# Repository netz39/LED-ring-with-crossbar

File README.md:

# LED ring with crossbar

This ring contains 32 addressable LEDs and 10 also addressable LEDs as crossbar.

This is part of [Stepper-Locking-System](https://github.com/netz39/Stepper-Locking-System).

The CAD models are here: [OnShape](https://cad.onshape.com/documents/e2d30949799f050b252632fe/w/72c412dc9c1a5764811a9783/e/a3e88e734353b2ea9fe2e731)
--

Requirements for v1.0
--

* sychronous addressable LEDs (APA102 or SK9822)
* two connectors, one input and one output for cascading
* two mounting holes

Pictures (v1.0)
--

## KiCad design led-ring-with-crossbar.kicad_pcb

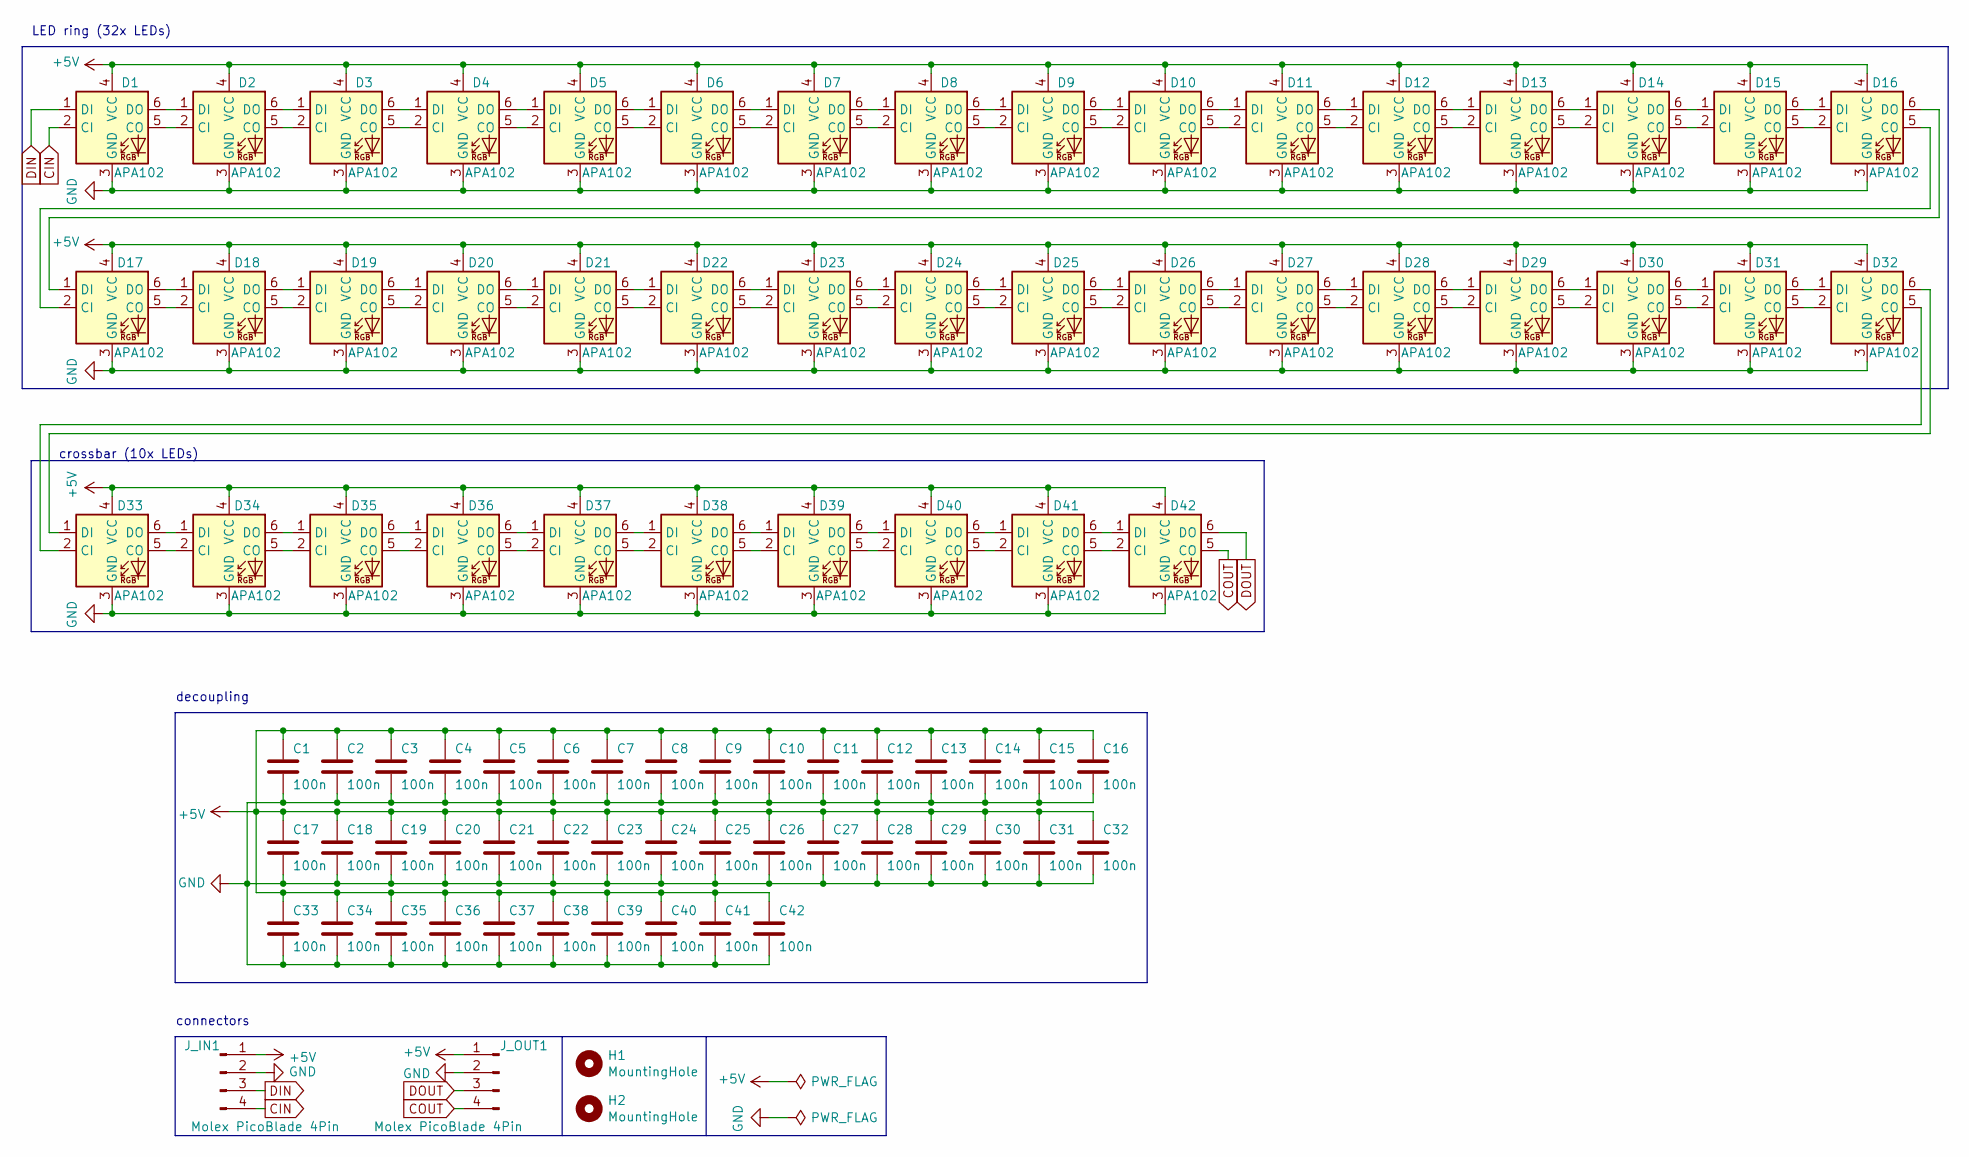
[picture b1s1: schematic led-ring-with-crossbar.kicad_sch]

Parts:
C1, C2, C3, C4, C5, C6, C7, C8, C9, C10, C11, C12, C13, C14, C15, C16, C17, C18, C19, C20, C21, C22, C23, C24, C25, C26, C27, C28, C29, C30, C31, C32, C33, C34, C35, C36, C37, C38, C39, C40, C41, C42: 100n; C_0603_1608Metric
D1, D2, D3, D4, D5, D6, D7, D8, D9, D10, D11, D12, D13, D14, D15, D16, D17, D18, D19, D20, D21, D22, D23, D24, D25, D26, D27, D28, D29, D30, D31, D32, D33, D34, D35, D36, D37, D38, D39, D40, D41, D42: APA102; LED_RGB_5050-6
H1, H2: MountingHole; MountingHole_3.2mm_M3_ISO7380_Keepout
J_IN1: Molex PicoBlade 4Pin; Molex_PicoBlade_53047-0410_1x04_P1.25mm_Vertical
J_OUT1: Molex PicoBlade 4Pin; Molex_PicoBlade_53047-0410_1x04_P1.25mm_Vertical

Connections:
+5V: C1.1, C2.1, C3.1, C4.1, C5.1, C6.1, C7.1, C8.1, C9.1, C10.1, C11.1, C12.1, C13.1, C14.1, C15.1, C16.1, C17.1, C18.1, C19.1, C20.1, C21.1, C22.1, C23.1, C24.1, C25.1, C26.1, C27.1, C28.1, C29.1, C30.1, C31.1, C32.1, C33.1, C34.1, C35.1, C36.1, C37.1, C38.1, C39.1, C40.1, C41.1, C42.1, D1.4 (VCC), D2.4 (VCC), D3.4 (VCC), D4.4 (VCC), D5.4 (VCC), D6.4 (VCC), D7.4 (VCC), D8.4 (VCC), D9.4 (VCC), D10.4 (VCC), D11.4 (VCC), D12.4 (VCC), D13.4 (VCC), D14.4 (VCC), D15.4 (VCC), D16.4 (VCC), D17.4 (VCC), D18.4 (VCC), D19.4 (VCC), D20.4 (VCC), D21.4 (VCC), D22.4 (VCC), D23.4 (VCC), D24.4 (VCC), D25.4 (VCC), D26.4 (VCC), D27.4 (VCC), D28.4 (VCC), D29.4 (VCC), D30.4 (VCC), D31.4 (VCC), D32.4 (VCC), D33.4 (VCC), D34.4 (VCC), D35.4 (VCC), D36.4 (VCC), D37.4 (VCC), D38.4 (VCC), D39.4 (VCC), D40.4 (VCC), D41.4 (VCC), D42.4 (VCC), J_IN1.1, J_OUT1.1
CIN: D1.2 (CI), J_IN1.4
COUT: D42.5 (CO), J_OUT1.4
DIN: D1.1 (DI), J_IN1.3
DOUT: D42.6 (DO), J_OUT1.3
GND: C1.2, C2.2, C3.2, C4.2, C5.2, C6.2, C7.2, C8.2, C9.2, C10.2, C11.2, C12.2, C13.2, C14.2, C15.2, C16.2, C17.2, C18.2, C19.2, C20.2, C21.2, C22.2, C23.2, C24.2, C25.2, C26.2, C27.2, C28.2, C29.2, C30.2, C31.2, C32.2, C33.2, C34.2, C35.2, C36.2, C37.2, C38.2, C39.2, C40.2, C41.2, C42.2, D1.3 (GND), D2.3 (GND), D3.3 (GND), D4.3 (GND), D5.3 (GND), D6.3 (GND), D7.3 (GND), D8.3 (GND), D9.3 (GND), D10.3 (GND), D11.3 (GND), D12.3 (GND), D13.3 (GND), D14.3 (GND), D15.3 (GND), D16.3 (GND), D17.3 (GND), D18.3 (GND), D19.3 (GND), D20.3 (GND), D21.3 (GND), D22.3 (GND), D23.3 (GND), D24.3 (GND), D25.3 (GND), D26.3 (GND), D27.3 (GND), D28.3 (GND), D29.3 (GND), D30.3 (GND), D31.3 (GND), D32.3 (GND), D33.3 (GND), D34.3 (GND), D35.3 (GND), D36.3 (GND), D37.3 (GND), D38.3 (GND), D39.3 (GND), D40.3 (GND), D41.3 (GND), D42.3 (GND), J_IN1.2, J_OUT1.2
unnamed: D1.5 (CO), D2.2 (CI)
unnamed: D1.6 (DO), D2.1 (DI)
unnamed: D2.5 (CO), D3.2 (CI)
unnamed: D2.6 (DO), D3.1 (DI)
unnamed: D3.5 (CO), D4.2 (CI)
unnamed: D3.6 (DO), D4.1 (DI)
unnamed: D4.5 (CO), D5.2 (CI)
unnamed: D4.6 (DO), D5.1 (DI)
unnamed: D5.5 (CO), D6.2 (CI)
unnamed: D5.6 (DO), D6.1 (DI)
unnamed: D6.5 (CO), D7.2 (CI)
unnamed: D6.6 (DO), D7.1 (DI)
unnamed: D7.5 (CO), D8.2 (CI)
unnamed: D7.6 (DO), D8.1 (DI)
unnamed: D8.5 (CO), D9.2 (CI)
unnamed: D8.6 (DO), D9.1 (DI)
unnamed: D9.6 (DO), D10.1 (DI)
unnamed: D9.5 (CO), D10.2 (CI)
unnamed: D10.5 (CO), D11.2 (CI)
unnamed: D10.6 (DO), D11.1 (DI)
unnamed: D11.5 (CO), D12.2 (CI)
unnamed: D11.6 (DO), D12.1 (DI)
unnamed: D12.5 (CO), D13.2 (CI)
unnamed: D12.6 (DO), D13.1 (DI)
unnamed: D13.5 (CO), D14.2 (CI)
unnamed: D13.6 (DO), D14.1 (DI)
unnamed: D14.5 (CO), D15.2 (CI)
unnamed: D14.6 (DO), D15.1 (DI)
unnamed: D15.5 (CO), D16.2 (CI)
unnamed: D15.6 (DO), D16.1 (DI)
unnamed: D16.5 (CO), D17.2 (CI)
unnamed: D16.6 (DO), D17.1 (DI)
unnamed: D17.5 (CO), D18.2 (CI)
unnamed: D17.6 (DO), D18.1 (DI)
unnamed: D18.5 (CO), D19.2 (CI)
unnamed: D18.6 (DO), D19.1 (DI)
unnamed: D19.5 (CO), D20.2 (CI)
unnamed: D19.6 (DO), D20.1 (DI)
unnamed: D20.5 (CO), D21.2 (CI)
unnamed: D20.6 (DO), D21.1 (DI)
unnamed: D21.5 (CO), D22.2 (CI)
unnamed: D21.6 (DO), D22.1 (DI)
unnamed: D22.5 (CO), D23.2 (CI)
unnamed: D22.6 (DO), D23.1 (DI)
unnamed: D23.5 (CO), D24.2 (CI)
unnamed: D23.6 (DO), D24.1 (DI)
unnamed: D24.5 (CO), D25.2 (CI)
unnamed: D24.6 (DO), D25.1 (DI)
unnamed: D25.5 (CO), D26.2 (CI)
unnamed: D25.6 (DO), D26.1 (DI)
unnamed: D26.5 (CO), D27.2 (CI)
unnamed: D26.6 (DO), D27.1 (DI)
unnamed: D27.5 (CO), D28.2 (CI)
unnamed: D27.6 (DO), D28.1 (DI)
unnamed: D28.5 (CO), D29.2 (CI)
unnamed: D28.6 (DO), D29.1 (DI)
unnamed: D29.5 (CO), D30.2 (CI)
unnamed: D29.6 (DO), D30.1 (DI)
unnamed: D30.5 (CO), D31.2 (CI)
unnamed: D30.6 (DO), D31.1 (DI)
unnamed: D31.5 (CO), D32.2 (CI)
unnamed: D31.6 (DO), D32.1 (DI)
unnamed: D32.5 (CO), D33.2 (CI)
unnamed: D32.6 (DO), D33.1 (DI)
unnamed: D33.5 (CO), D34.2 (CI)
unnamed: D33.6 (DO), D34.1 (DI)
unnamed: D34.5 (CO), D35.2 (CI)
unnamed: D34.6 (DO), D35.1 (DI)
unnamed: D35.5 (CO), D36.2 (CI)
unnamed: D35.6 (DO), D36.1 (DI)
unnamed: D36.5 (CO), D37.2 (CI)
unnamed: D36.6 (DO), D37.1 (DI)
unnamed: D37.5 (CO), D38.2 (CI)
unnamed: D37.6 (DO), D38.1 (DI)
unnamed: D38.5 (CO), D39.2 (CI)
unnamed: D38.6 (DO), D39.1 (DI)
unnamed: D39.5 (CO), D40.2 (CI)
unnamed: D39.6 (DO), D40.1 (DI)
unnamed: D40.5 (CO), D41.2 (CI)
unnamed: D40.6 (DO), D41.1 (DI)
unnamed: D41.5 (CO), D42.2 (CI)
unnamed: D41.6 (DO), D42.1 (DI)

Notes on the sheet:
connectors
LED ring (32x LEDs)
crossbar (10x LEDs)
decoupling

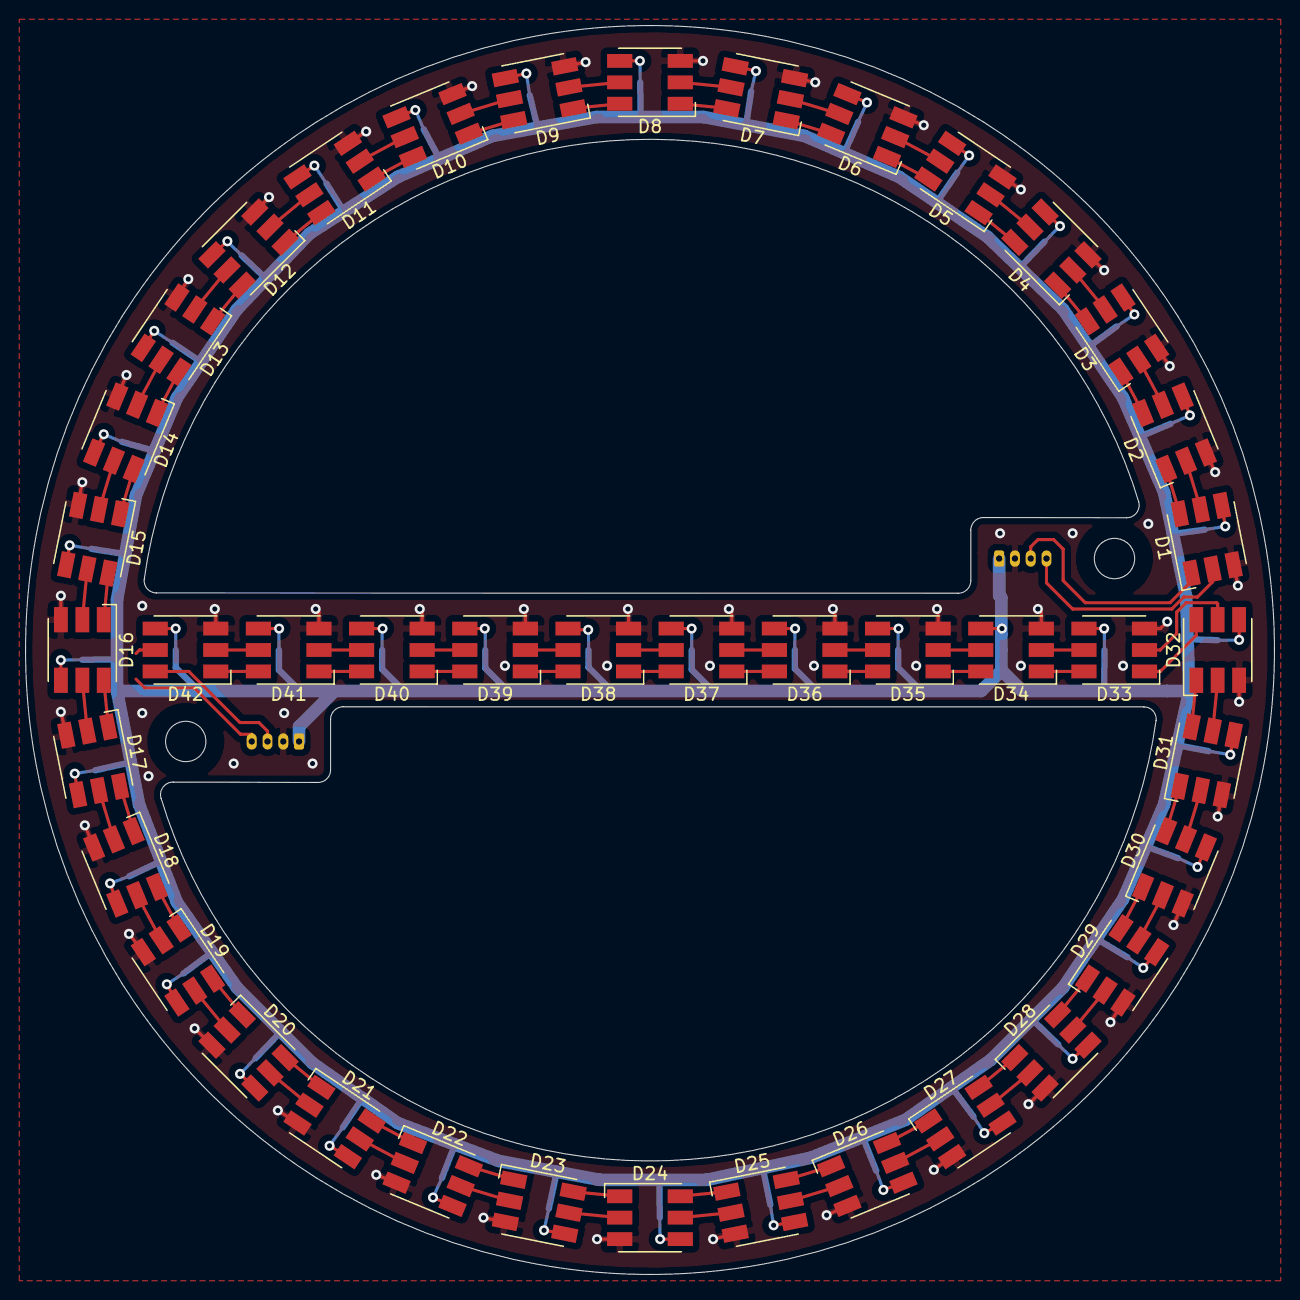
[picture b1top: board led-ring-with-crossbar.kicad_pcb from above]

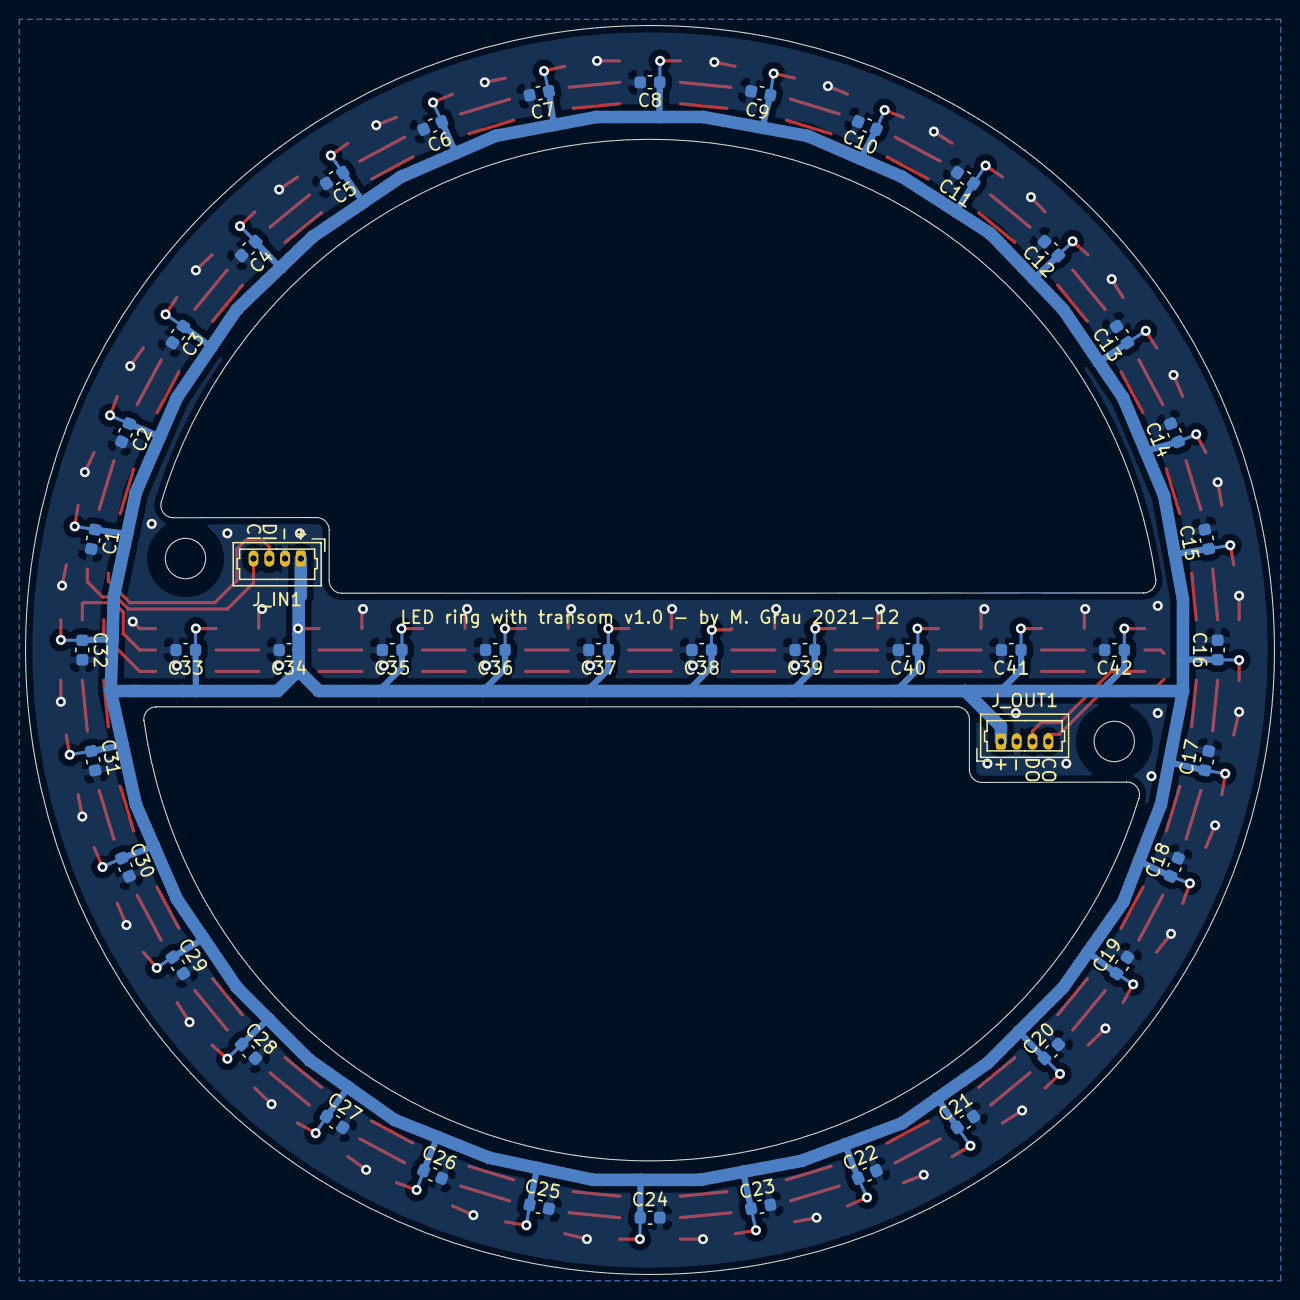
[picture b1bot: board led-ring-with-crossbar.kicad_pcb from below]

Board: 2 copper layers, 99.0 x 99.0 mm, 88 parts (44 on the bottom side), 88 nets.

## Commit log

2021-11-25 Add schematic
2021-11-26 Finish PCB
2021-11-26 Rename transom to crossbar
2021-11-26 Add ReadMe
